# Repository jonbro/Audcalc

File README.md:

# AudCalc

AudCalc is a portable synthesizer and sequencer.

It has 8 voices which can switch between synthesis (using Mutable Instruments Braids cores) and sampling. The sequencer supports parameter locks, conditional triggers, and various time signatures and loop lengths. There are also two built in effects sends for building a full track. It's fun to jam with by itself, and can link into your larger portable music setup via midi or cv clock.

[Website](https://audcalc.jonathanbrodsky.com) | [Manual](https://audcalc.jonathanbrodsky.com/docs.html) | [Shop](https://thegoblingroup.com/products/audcalc) | [Contact](https://audcalc.jonathanbrodsky.com/contact.html)

## Specifications

### Synthesizer

- Many different oscillators from MI Braids
- 2 assignable AD envelopes
- Lowpass filter
- Volume, pan, legato, finetune
- 2 effects sends (delay & reverb)
- Assignable LFO
- Simple sampler (sampling via line in or onboard mic)
- 16 patches, 8 simultaneous monophonic voices

### Sequencer

- 16 patterns, with assignable lengths from 1-64 steps
- 4096 pattern lock locations for overriding synthesizer settings per step
- Each of the 16 patches can run at 2x-1/8 bpm rate, with some fun subdivisions
- Conditional triggers
- Pattern chaining
- Step ratcheting / retriggers

### Hardware

- RP2040 core
- 1000mAh rechargeable and replaceable battery, USB-C charging
- TRS midi in/out, audio in/out (3.5mm TRS), USB midi
- 100x65x25mm - approximately the size of a cassette tape box + knob height
- Body made with FDM black PLA, buttons with FDM translucent TPU
- FR4 (circuitboard) faceplate
- OLED display

## Building one

The BOM is contained within the Hardware KiCad project, ready for assembly via JLCPCB.
There are several additional items that must be sourced and assembled:

| part                         | count | mfg part number | link                                                  | notes                                                                                 |
|------------------------------|-------|-----------------|-------------------------------------------------------|---------------------------------------------------------------------------------------|
| oled screen (128x32)         | 1     | ssd1306         | https://www.aliexpress.com/item/4000842671330.html    | I'm using the white / solderable version.                                             |
| battery (50x34x5mm, ~1000mAh) | 1    | 503450          | search for "503450" with a JST-PH connector           | Widely available from many vendors. Confirm the correct polarity before using.        |
| m2 4mm f-f standoff          | 4     |                 | https://www.aliexpress.com/item/1005002145042844.html |                                                                                       |
| m2 6mm m-f standoff          | 4     |                 | https://www.aliexpress.com/item/1005002145042844.html |                                                                                       |
| m2 3mm hex head bolt (black) | 8     |                 | https://www.aliexpress.com/item/10000148429238.html   |                                                                                       |

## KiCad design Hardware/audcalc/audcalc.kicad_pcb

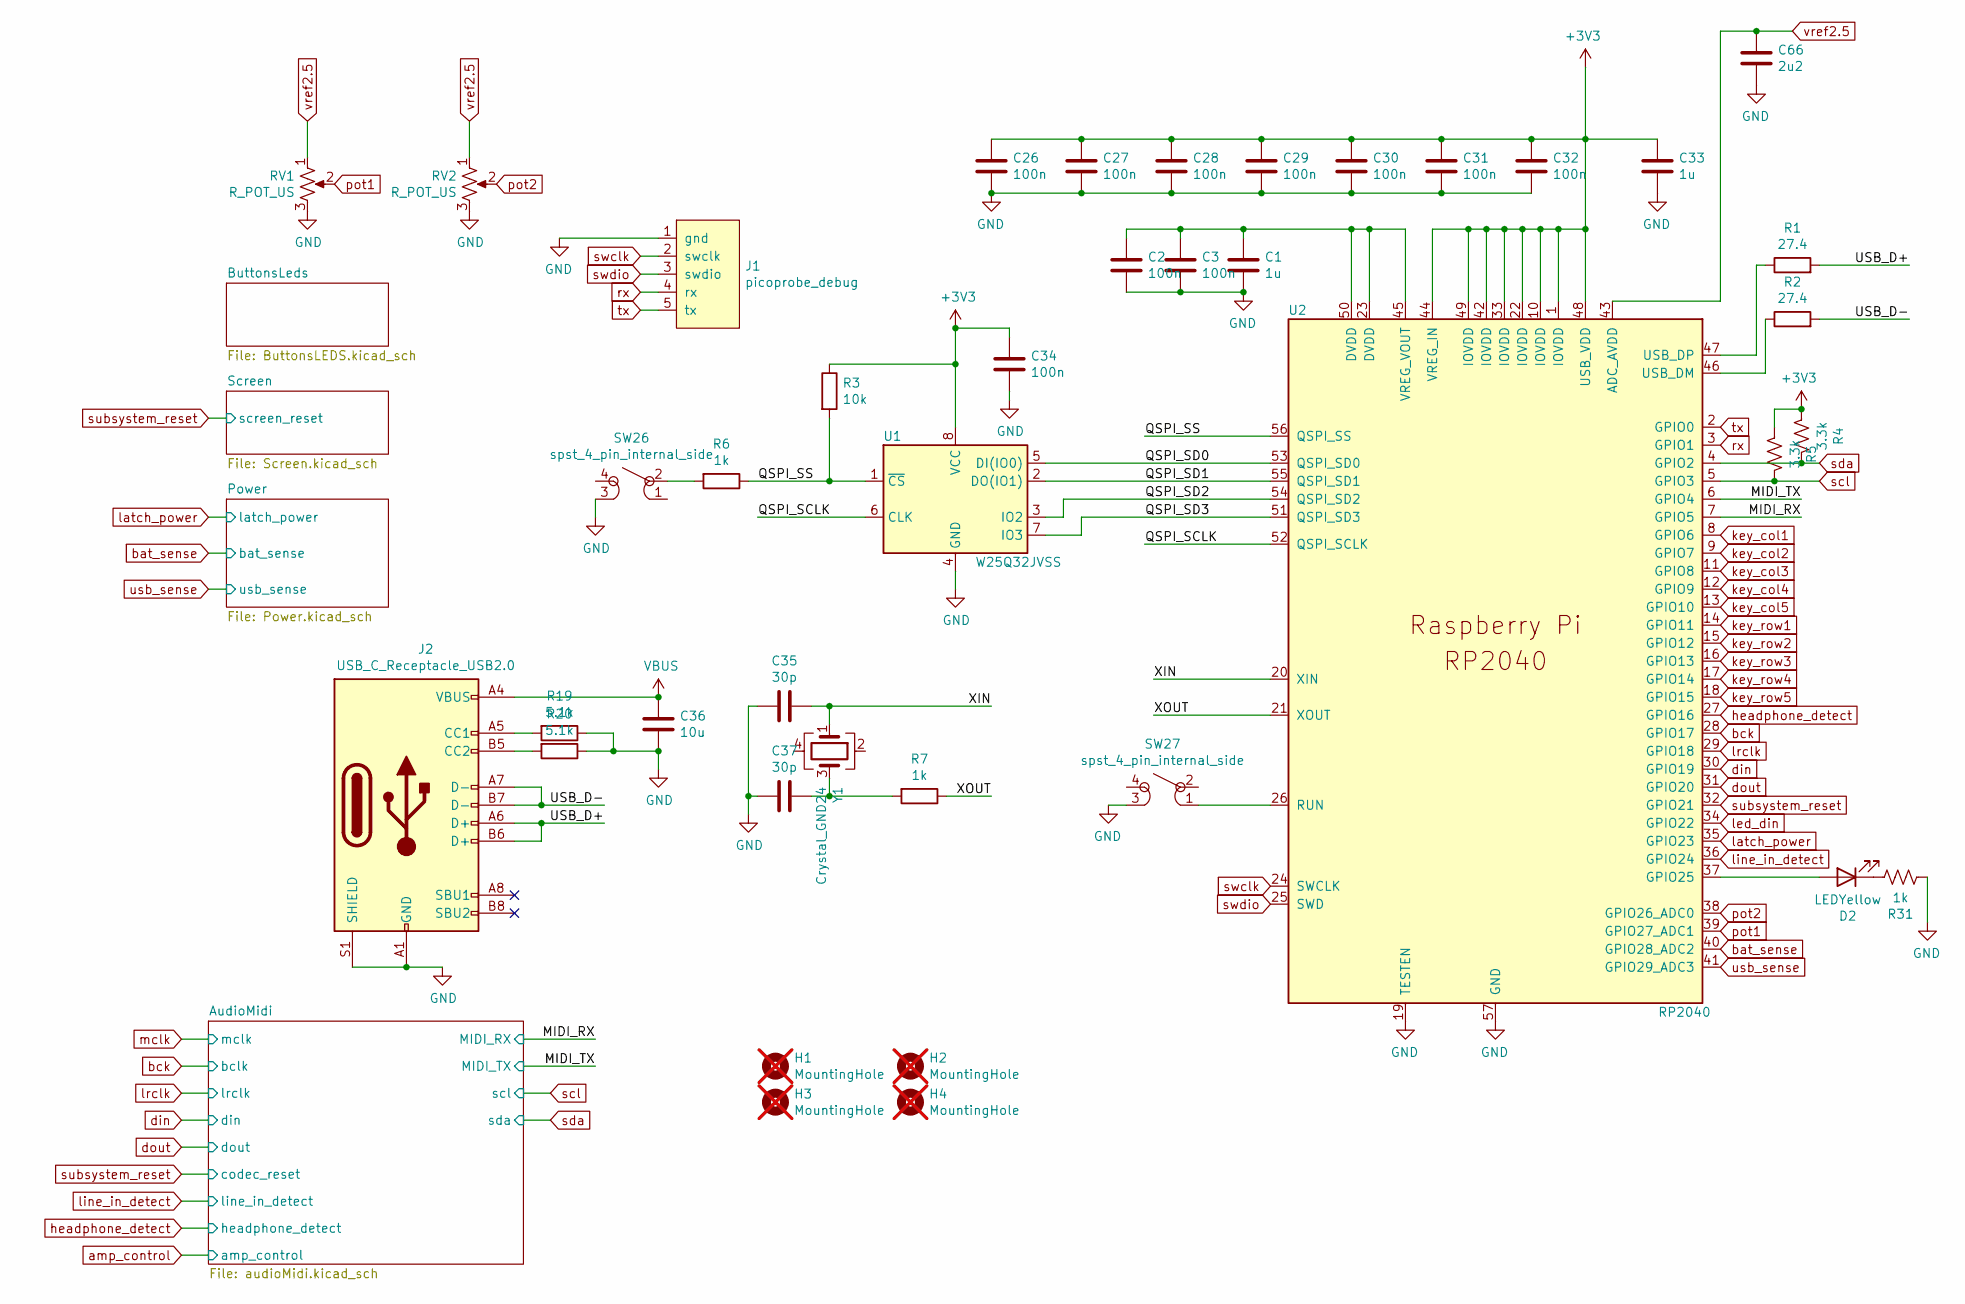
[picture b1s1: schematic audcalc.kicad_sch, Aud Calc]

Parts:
C1, C33: 1u; C_0402_1005Metric; LCSC C52923
C2, C3, C26, C27, C28, C29, C30, C31, C32, C34: 100n; C_0402_1005Metric; LCSC C307331
C35, C37: 30p; C_0402_1005Metric; LCSC C1570
C36: 10u; C_0402_1005Metric; LCSC C15525
C66: 2u2; C_0402_1005Metric; LCSC C12530
D2: LEDYellow; LED_0603; LCSC C89811
H1, H2, H3, H4: MountingHole; MountingHole_2.2mm_M2; not fitted
J1: picoprobe_debug; pico debug header
J2: USB_C_Receptacle_USB2.0; USB-C_SMD-TYPE-C-31-M-12; LCSC C165948
R1, R2: 27.4; R_0402_1005Metric_nosilk; LCSC C31439
R3: 10k; R_0402_1005Metric_nosilk; LCSC C25744
R4, R5: 3.3k; R_0402_1005Metric_nosilk; LCSC C25890
R6, R7, R31: 1k; R_0402_1005Metric_nosilk; LCSC C11702
R19, R20: 5.1k; R_0402_1005Metric_nosilk; LCSC C25905
RV1, RV2: R_POT_US; Potentiometer_Alps_RK09K_Horizontal; LCSC C209779
SW26, SW27: spst_4_pin_internal_side; SKSCLDE010; LCSC C115362
U1: W25Q32JVSS; SOIJ-8_5.3x5.3mm_Pitch1.27mm; LCSC C97521
U2: RP2040; RP2040-QFN-56; LCSC C2040
Y1: Crystal_GND24; Crystal_SMD_3225-4pin_3.2x2.5mm; LCSC C5332006

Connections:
+3V3: C26.1, C27.1, C28.1, C29.1, C30.1, C31.1, C32.1, C33.1, C34.1, R3.1, R4.1, R5.1, U1.8 (VCC), U2.1 (IOVDD), U2.10 (IOVDD), U2.22 (IOVDD), U2.33 (IOVDD), U2.42 (IOVDD), U2.44 (VREG_IN), U2.48 (USB_VDD), U2.49 (IOVDD); also elsewhere on the board
/MIDI_RX: U2.7 (GPIO5); also elsewhere on the board
/MIDI_TX: U2.6 (GPIO4); also elsewhere on the board
/QSPI_SCLK: U1.6 (CLK), U2.52 (QSPI_SCLK)
/QSPI_SD0: U1.5 (DI(IO0)), U2.53 (QSPI_SD0)
/QSPI_SD1: U1.2 (DO(IO1)), U2.55 (QSPI_SD1)
/QSPI_SD2: U1.3 (IO2), U2.54 (QSPI_SD2)
/QSPI_SD3: U1.7 (IO3), U2.51 (QSPI_SD3)
/QSPI_SS: R3.2, R6.1, U1.1 (~CS), U2.56 (QSPI_SS)
/USB_D+: J2.A6 (D+), J2.B6 (D+), R1.2
/USB_D-: J2.A7 (D-), J2.B7 (D-), R2.2
/XIN: C35.1, U2.20 (XIN), Y1.1
/XOUT: R7.1, U2.21 (XOUT)
GND: C1.2, C2.2, C3.2, C26.2, C27.2, C28.2, C29.2, C30.2, C31.2, C32.2, C33.2, C34.2, C35.2, C36.2, C37.2, C66.2, J1.1 (gnd), J2.A1 (GND), J2.A12 (GND), J2.B1 (GND), J2.B12 (GND), J2.S1 (SHIELD), R19.1, R20.1, R31.2, RV1.3, RV2.3, SW26.3, SW27.3, U1.4 (GND), U2.19 (TESTEN), U2.57 (GND); also elsewhere on the board
unnamed: C37.1, R7.2, Y1.3
unnamed: D2.2 (A), U2.37 (GPIO25)
unnamed: D2.1 (K), R31.1
unnamed: J2.A5 (CC1), R19.2
unnamed: J2.B5 (CC2), R20.2
unnamed: R6.2, SW26.2
unnamed: SW27.1, U2.26 (RUN)
unnamed: R2.1, U2.46 (USB_DM)
unnamed: R1.1, U2.47 (USB_DP)
unnamed: C1.1, C2.1, C3.1, U2.23 (DVDD), U2.45 (VREG_VOUT), U2.50 (DVDD)
VBUS: C36.1, J2.A4 (VBUS), J2.A9 (VBUS), J2.B4 (VBUS), J2.B9 (VBUS); also elsewhere on the board
bat_sense: U2.40 (GPIO28_ADC2); also elsewhere on the board
bck: U2.28 (GPIO17); also elsewhere on the board
din: U2.30 (GPIO19); also elsewhere on the board
dout: U2.31 (GPIO20); also elsewhere on the board
headphone_detect: U2.27 (GPIO16); also elsewhere on the board
key_col1: U2.8 (GPIO6); also elsewhere on the board
key_col2: U2.9 (GPIO7); also elsewhere on the board
key_col3: U2.11 (GPIO8); also elsewhere on the board
key_col4: U2.12 (GPIO9); also elsewhere on the board
key_col5: U2.13 (GPIO10); also elsewhere on the board
key_row1: U2.14 (GPIO11); also elsewhere on the board
key_row2: U2.15 (GPIO12); also elsewhere on the board
key_row3: U2.16 (GPIO13); also elsewhere on the board
key_row4: U2.17 (GPIO14); also elsewhere on the board
key_row5: U2.18 (GPIO15); also elsewhere on the board
latch_power: U2.35 (GPIO23); also elsewhere on the board
led_din: U2.34 (GPIO22); also elsewhere on the board
line_in_detect: U2.36 (GPIO24); also elsewhere on the board
lrclk: U2.29 (GPIO18); also elsewhere on the board
pot1: RV1.2, U2.39 (GPIO27_ADC1)
pot2: RV2.2, U2.38 (GPIO26_ADC0)
rx: J1.4 (rx), U2.3 (GPIO1)
scl: R5.2, U2.5 (GPIO3); also elsewhere on the board
sda: R4.2, U2.4 (GPIO2); also elsewhere on the board
subsystem_reset: U2.32 (GPIO21); also elsewhere on the board
swclk: J1.2 (swclk), U2.24 (SWCLK)
swdio: J1.3 (swdio), U2.25 (SWD)
tx: J1.5 (tx), U2.2 (GPIO0)
usb_sense: U2.41 (GPIO29_ADC3); also elsewhere on the board
vref2.5: C66.1, RV1.1, RV2.1, U2.43 (ADC_AVDD); also elsewhere on the board

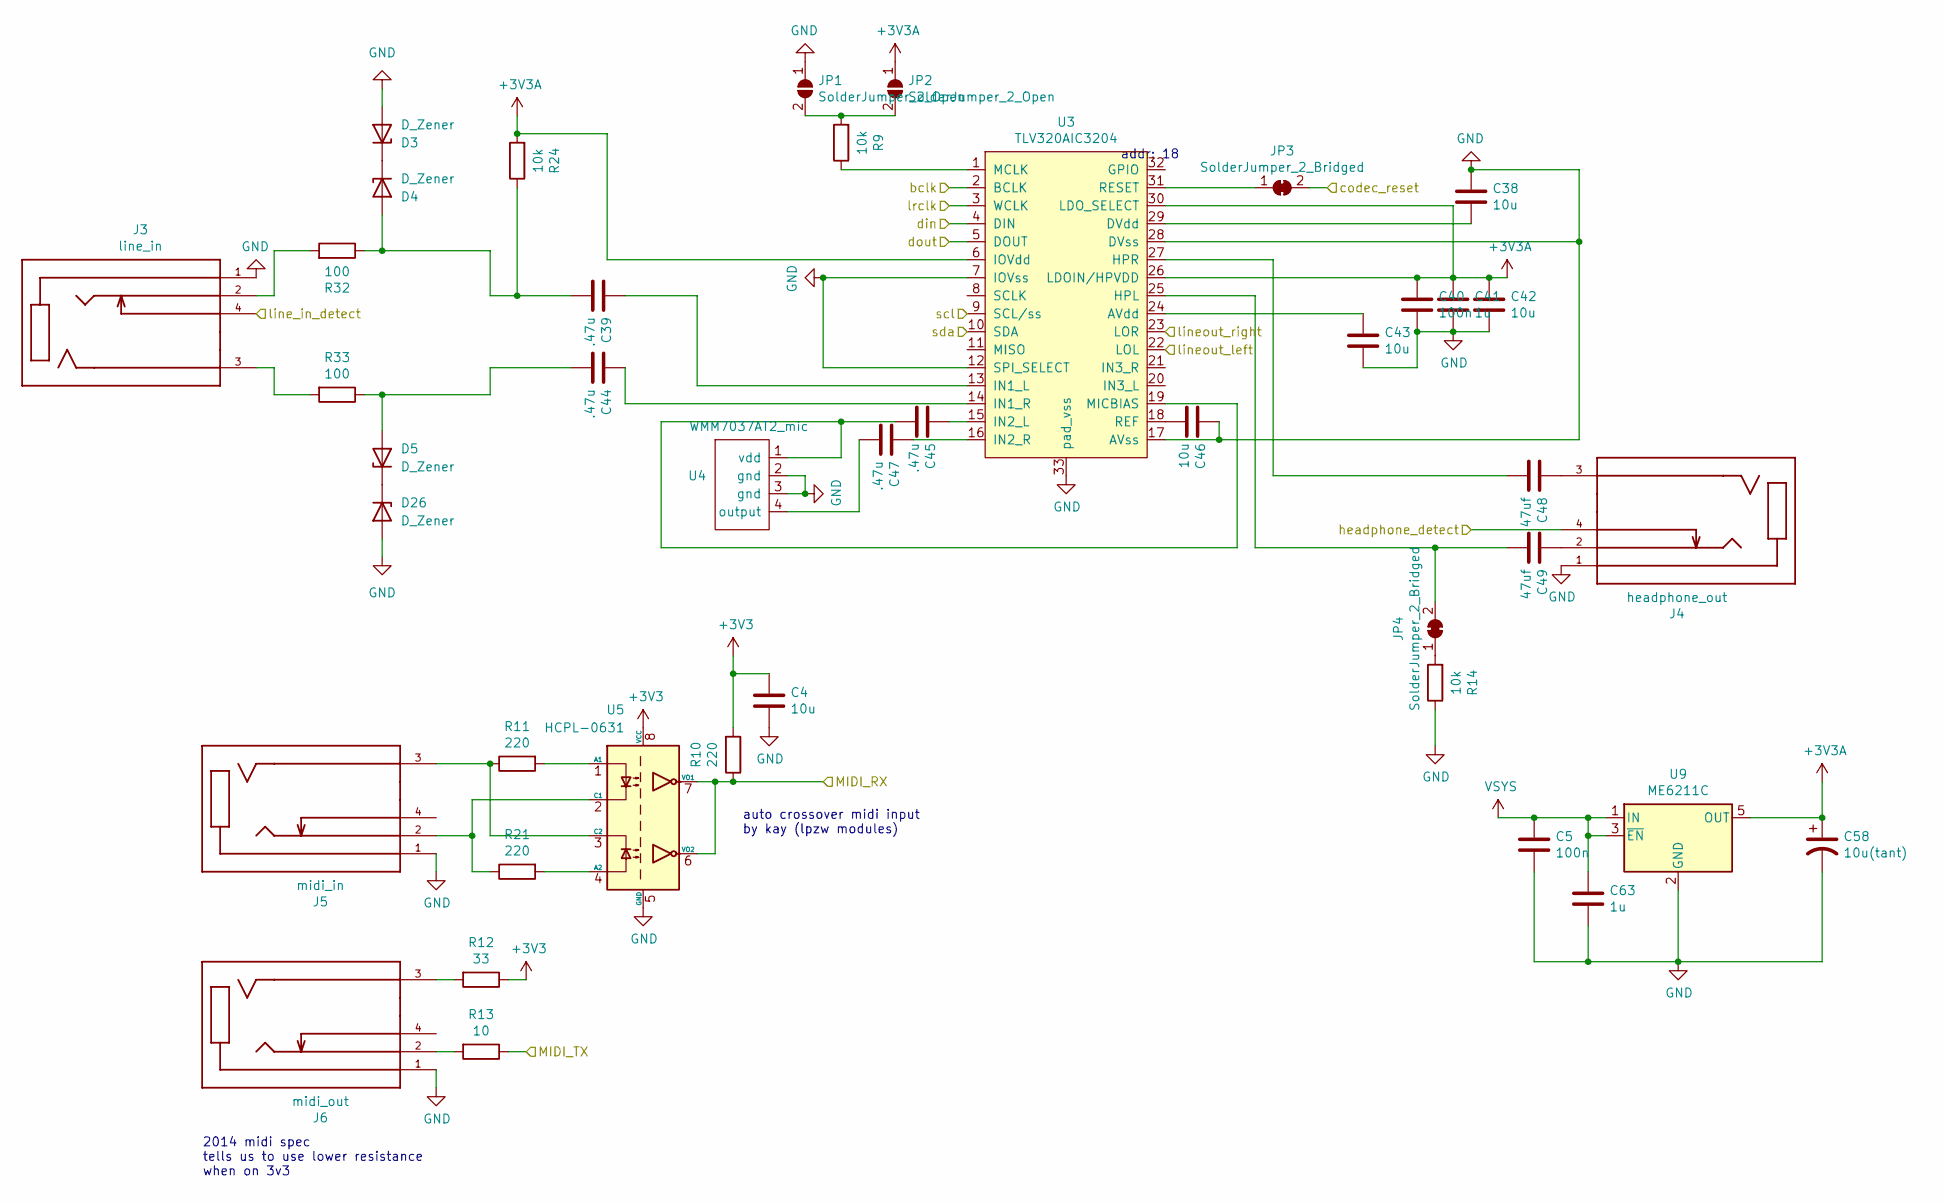
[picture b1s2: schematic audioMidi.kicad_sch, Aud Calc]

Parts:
C4, C38, C42, C43, C46: 10u; C_0402_1005Metric; LCSC C15525
C5, C40: 100n; C_0402_1005Metric; LCSC C307331
C39, C44, C45, C47: .47u; C_0603_nosilk; LCSC C1623
C41, C63: 1u; C_0402_1005Metric; LCSC C52923
C48, C49: 47uf; C_1206; LCSC C96123
C58: 10u(tant); CP_Tantalum_Case-A_EIA-3216-18_Reflow; LCSC C7171
D3, D4, D5, D26: D_Zener; D_SOD-323F; LCSC C52056
J3: line_in; HRO-PJ-327C-A; LCSC C145813
J4: headphone_out; HRO-PJ-327C-A; LCSC C145813
J5: midi_in; HRO-PJ-327C-A; LCSC C145813
J6: midi_out; HRO-PJ-327C-A; LCSC C145813
JP1, JP2: SolderJumper_2_Open; SolderJumper-2_P1.3mm_Open_RoundedPad1.0x1.5mm
JP3, JP4: SolderJumper_2_Bridged; SolderJumper-2_P1.3mm_Bridged_Pad1.0x1.5mm
R9, R14, R24: 10k; R_0402_1005Metric_nosilk; LCSC C25744
R10, R11, R21: 220; R_0402_1005Metric_nosilk; LCSC C25091
R12: 33; R_0402_1005Metric_nosilk; LCSC C25105
R13: 10; R_0402_1005Metric_nosilk; LCSC C25077
R32, R33: 100; R_0402_1005Metric; LCSC C25076
U3: TLV320AIC3204; QFN-32-1EP_5x5mm_Pitch0.5mm; LCSC C9925
U4: WMM7037AT2_mic; LGA-4 (3x3.8); LCSC C140705
U5: HCPL-0631; SOIC-8_3.9x4.9mm_P1.27mm; LCSC C43949
U9: ME6211C; SOT-23-5; LCSC C82942

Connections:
+3V3: C4.1, R10.2, R12.1, U5.8 (VCC); also elsewhere on the board
+3V3A: C40.1, C41.1, C42.1, C58.1, JP2.1 (A), R24.2, U3.6 (IOVdd), U3.26 (LDOIN/HPVDD), U3.30 (LDO_SELECT), U9.5 (OUT)
/AudioMidi/lineout_left: U3.22 (LOL)
/AudioMidi/lineout_right: U3.23 (LOR)
/MIDI_RX: R10.1, U5.6 (VO2), U5.7 (VO1); also elsewhere on the board
/MIDI_TX: R13.1; also elsewhere on the board
GND: C4.2, C5.2, C38.1, C40.2, C41.2, C42.2, C43.2, C46.1, C58.2, C63.2, D3.2 (A), D26.2 (A), J3.1 (SLEEVE), J4.1 (SLEEVE), J5.1 (SLEEVE), J6.1 (SLEEVE), JP1.1 (A), R14.1, U3.7 (IOVss), U3.12 (SPI_SELECT), U3.17 (AVss), U3.28 (DVss), U3.33 (pad_vss), U4.2 (gnd), U4.3 (gnd), U5.5 (GND), U9.2 (GND); also elsewhere on the board
unnamed: D3.1 (K), D4.1 (K)
unnamed: C39.2, D4.2 (A), R24.1, R32.1
unnamed: C44.2, D5.2 (A), R33.1
unnamed: D5.1 (K), D26.1 (K)
unnamed: J3.3 (RING), R33.2
unnamed: J3.2 (TIP_1), R32.2
unnamed: C48.1, J4.3 (RING)
unnamed: C49.1, J4.2 (TIP_1)
unnamed: J5.3 (RING), R11.1, U5.3 (C2)
unnamed: J5.2 (TIP_1), R21.1, U5.2 (C1)
unnamed: J6.3 (RING), R12.2
unnamed: J6.2 (TIP_1), R13.2
unnamed: JP1.2 (B), JP2.2 (B), R9.2
unnamed: JP3.1 (A), U3.31 (RESET)
unnamed: JP4.1 (A), R14.2
unnamed: C49.2, JP4.2 (B), U3.25 (HPL)
unnamed: C43.1, U3.24 (AVdd)
unnamed: C38.2, U3.29 (DVdd)
unnamed: C48.2, U3.27 (HPR)
unnamed: C39.1, U3.13 (IN1_L)
unnamed: C44.1, U3.14 (IN1_R)
unnamed: C45.1, U3.15 (IN2_L)
unnamed: C47.1, U3.16 (IN2_R)
unnamed: R9.1, U3.1 (MCLK)
unnamed: C45.2, U3.19 (MICBIAS), U4.1 (vdd)
unnamed: C46.2, U3.18 (REF)
unnamed: C47.2, U4.4 (output)
unnamed: R11.2, U5.1 (A1)
unnamed: R21.2, U5.4 (A2)
VSYS: C5.1, C63.1, U9.1 (IN), U9.3 (~EN); also elsewhere on the board
bck: U3.2 (BCLK); also elsewhere on the board
din: U3.4 (DIN); also elsewhere on the board
dout: U3.5 (DOUT); also elsewhere on the board
headphone_detect: J4.4 (TIP_SWITCH); also elsewhere on the board
line_in_detect: J3.4 (TIP_SWITCH); also elsewhere on the board
lrclk: U3.3 (WCLK); also elsewhere on the board
scl: U3.9 (SCL/ss); also elsewhere on the board
sda: U3.10 (SDA); also elsewhere on the board
subsystem_reset: JP3.2 (B); also elsewhere on the board

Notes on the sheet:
2014 midi spec tells us to use lower resistance when on 3v3
addr: 18
auto crossover midi input by kay (lpzw modules)

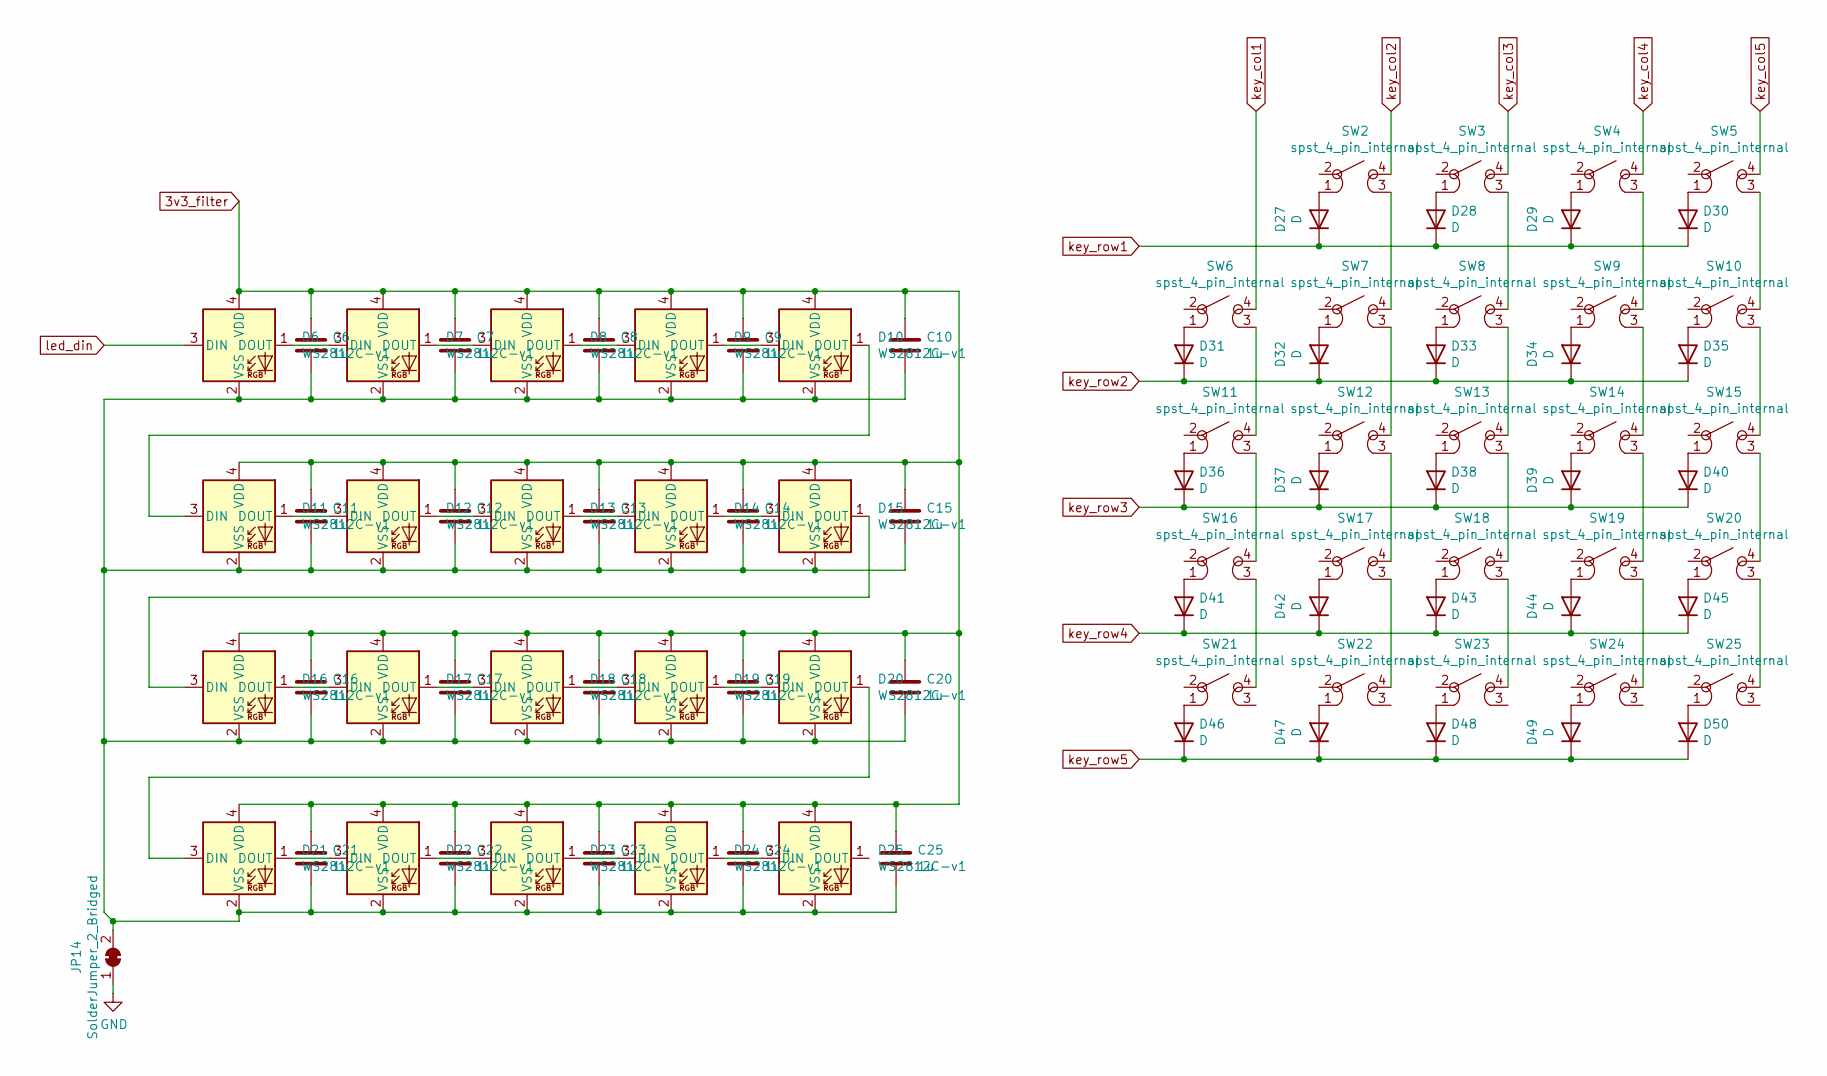
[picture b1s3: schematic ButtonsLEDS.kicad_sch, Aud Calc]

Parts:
C6, C7, C8, C9, C10, C11, C12, C13, C14, C15, C16, C17, C18, C19, C20, C21, C22, C23, C24, C25: 1u; C_0402_1005Metric; LCSC C52923
D6, D7, D8, D9, D10, D11, D12, D13, D14, D15, D16, D17, D18, D19, D20, D21, D22, D23, D24, D25: WS2812C-v1; ws2812b-2020-lightpipe; LCSC C2976072
D27, D28, D29, D30, D31, D32, D33, D34, D35, D36, D37, D38, D39, D40, D41, D42, D43, D44, D45, D46, D47, D48, D49, D50: D; D_SOD-323F_less_silk; LCSC C2128
JP14: SolderJumper_2_Bridged; SolderJumper-2_P1.3mm_Bridged_Pad1.0x1.5mm
SW2, SW3, SW4, SW5, SW6, SW7, SW8, SW9, SW10, SW11, SW12, SW13, SW14, SW15, SW16, SW17, SW18, SW19, SW20, SW21, SW22, SW23, SW24, SW25: spst_4_pin_internal; ts1187; LCSC C318884

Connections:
3v3_filter: C6.1, C7.1, C8.1, C9.1, C10.1, C11.1, C12.1, C13.1, C14.1, C15.1, C16.1, C17.1, C18.1, C19.1, C20.1, C21.1, C22.1, C23.1, C24.1, C25.1, D6.4 (VDD), D7.4 (VDD), D8.4 (VDD), D9.4 (VDD), D10.4 (VDD), D11.4 (VDD), D12.4 (VDD), D13.4 (VDD), D14.4 (VDD), D15.4 (VDD), D16.4 (VDD), D17.4 (VDD), D18.4 (VDD), D19.4 (VDD), D20.4 (VDD), D21.4 (VDD), D22.4 (VDD), D23.4 (VDD), D24.4 (VDD), D25.4 (VDD); also elsewhere on the board
GND: JP14.1 (A); also elsewhere on the board
unnamed: D6.1 (DOUT), D7.3 (DIN)
unnamed: D7.1 (DOUT), D8.3 (DIN)
unnamed: D8.1 (DOUT), D9.3 (DIN)
unnamed: D9.1 (DOUT), D10.3 (DIN)
unnamed: D10.1 (DOUT), D11.3 (DIN)
unnamed: C6.2, C7.2, C8.2, C9.2, C10.2, C11.2, C12.2, C13.2, C14.2, C15.2, C16.2, C17.2, C18.2, C19.2, C20.2, C21.2, C22.2, C23.2, C24.2, C25.2, D6.2 (VSS), D7.2 (VSS), D8.2 (VSS), D9.2 (VSS), D10.2 (VSS), D11.2 (VSS), D12.2 (VSS), D13.2 (VSS), D14.2 (VSS), D15.2 (VSS), D16.2 (VSS), D17.2 (VSS), D18.2 (VSS), D19.2 (VSS), D20.2 (VSS), D21.2 (VSS), D22.2 (VSS), D23.2 (VSS), D24.2 (VSS), D25.2 (VSS), JP14.2 (B)
unnamed: D11.1 (DOUT), D12.3 (DIN)
unnamed: D12.1 (DOUT), D13.3 (DIN)
unnamed: D13.1 (DOUT), D14.3 (DIN)
unnamed: D14.1 (DOUT), D15.3 (DIN)
unnamed: D15.1 (DOUT), D16.3 (DIN)
unnamed: D16.1 (DOUT), D17.3 (DIN)
unnamed: D17.1 (DOUT), D18.3 (DIN)
unnamed: D18.1 (DOUT), D19.3 (DIN)
unnamed: D19.1 (DOUT), D20.3 (DIN)
unnamed: D20.1 (DOUT), D21.3 (DIN)
unnamed: D21.1 (DOUT), D22.3 (DIN)
unnamed: D22.1 (DOUT), D23.3 (DIN)
unnamed: D23.1 (DOUT), D24.3 (DIN)
unnamed: D24.1 (DOUT), D25.3 (DIN)
unnamed: D27.2 (A), SW2.1
unnamed: D28.2 (A), SW3.1
unnamed: D29.2 (A), SW4.1
unnamed: D30.2 (A), SW5.1
unnamed: D31.2 (A), SW6.1
unnamed: D32.2 (A), SW7.1
unnamed: D33.2 (A), SW8.1
unnamed: D34.2 (A), SW9.1
unnamed: D35.2 (A), SW10.1
unnamed: D36.2 (A), SW11.1
unnamed: D37.2 (A), SW12.1
unnamed: D38.2 (A), SW13.1
unnamed: D39.2 (A), SW14.1
unnamed: D40.2 (A), SW15.1
unnamed: D41.2 (A), SW16.1
unnamed: D42.2 (A), SW17.1
unnamed: D43.2 (A), SW18.1
unnamed: D44.2 (A), SW19.1
unnamed: D45.2 (A), SW20.1
unnamed: D46.2 (A), SW21.1
unnamed: D47.2 (A), SW22.1
unnamed: D48.2 (A), SW23.1
unnamed: D49.2 (A), SW24.1
unnamed: D50.2 (A), SW25.1
unnamed: SW2.3, SW7.4
unnamed: SW3.3, SW8.4
unnamed: SW4.3, SW9.4
unnamed: SW10.3, SW15.4
unnamed: SW5.3, SW10.4
unnamed: SW11.3, SW16.4
unnamed: SW6.3, SW11.4
unnamed: SW12.3, SW17.4
unnamed: SW7.3, SW12.4
unnamed: SW13.3, SW18.4
unnamed: SW8.3, SW13.4
unnamed: SW14.3, SW19.4
unnamed: SW9.3, SW14.4
unnamed: SW15.3, SW20.4
unnamed: SW16.3, SW21.4
unnamed: SW17.3, SW22.4
unnamed: SW18.3, SW23.4
unnamed: SW19.3, SW24.4
unnamed: SW20.3, SW25.4
key_col1: SW6.4; also elsewhere on the board
key_col2: SW2.4; also elsewhere on the board
key_col3: SW3.4; also elsewhere on the board
key_col4: SW4.4; also elsewhere on the board
key_col5: SW5.4; also elsewhere on the board
key_row1: D27.1 (K), D28.1 (K), D29.1 (K), D30.1 (K); also elsewhere on the board
key_row2: D31.1 (K), D32.1 (K), D33.1 (K), D34.1 (K), D35.1 (K); also elsewhere on the board
key_row3: D36.1 (K), D37.1 (K), D38.1 (K), D39.1 (K), D40.1 (K); also elsewhere on the board
key_row4: D41.1 (K), D42.1 (K), D43.1 (K), D44.1 (K), D45.1 (K); also elsewhere on the board
key_row5: D46.1 (K), D47.1 (K), D48.1 (K), D49.1 (K), D50.1 (K); also elsewhere on the board
led_din: D6.3 (DIN); also elsewhere on the board

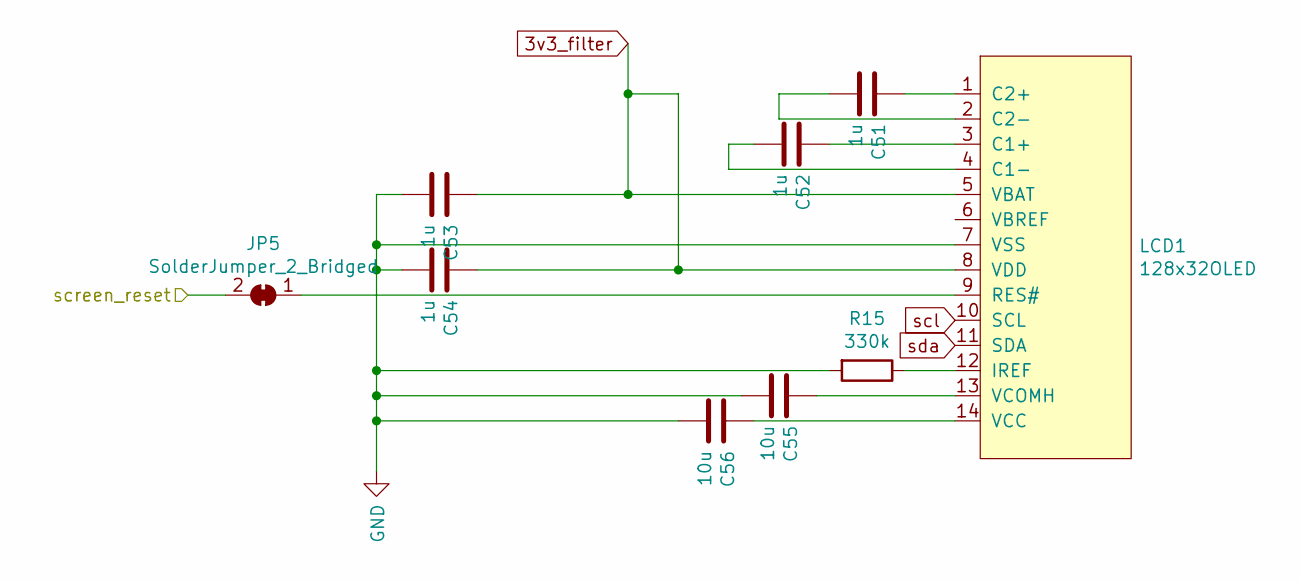
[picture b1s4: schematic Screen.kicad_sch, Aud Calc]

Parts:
C51, C52, C53, C54: 1u; C_0402_1005Metric; LCSC C52923
C55, C56: 10u; C_0402_1005Metric; LCSC C15525
JP5: SolderJumper_2_Bridged; SolderJumper-2_P1.3mm_Bridged_Pad1.0x1.5mm
LCD1: 128x32OLED; oled_ssd1306_14pin_91
R15: 330k; R_0402_1005Metric; LCSC C25778

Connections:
3v3_filter: C53.1, C54.1, LCD1.5 (VBAT), LCD1.8 (VDD); also elsewhere on the board
GND: C53.2, C54.2, C55.2, C56.2, LCD1.7 (VSS), R15.2; also elsewhere on the board
unnamed: JP5.1 (A), LCD1.9 (RES#)
unnamed: C52.1, LCD1.3 (C1+)
unnamed: C52.2, LCD1.4 (C1-)
unnamed: C51.1, LCD1.1 (C2+)
unnamed: C51.2, LCD1.2 (C2-)
unnamed: LCD1.12 (IREF), R15.1
unnamed: C56.1, LCD1.14 (VCC)
unnamed: C55.1, LCD1.13 (VCOMH)
scl: LCD1.10 (SCL); also elsewhere on the board
sda: LCD1.11 (SDA); also elsewhere on the board
subsystem_reset: JP5.2 (B); also elsewhere on the board

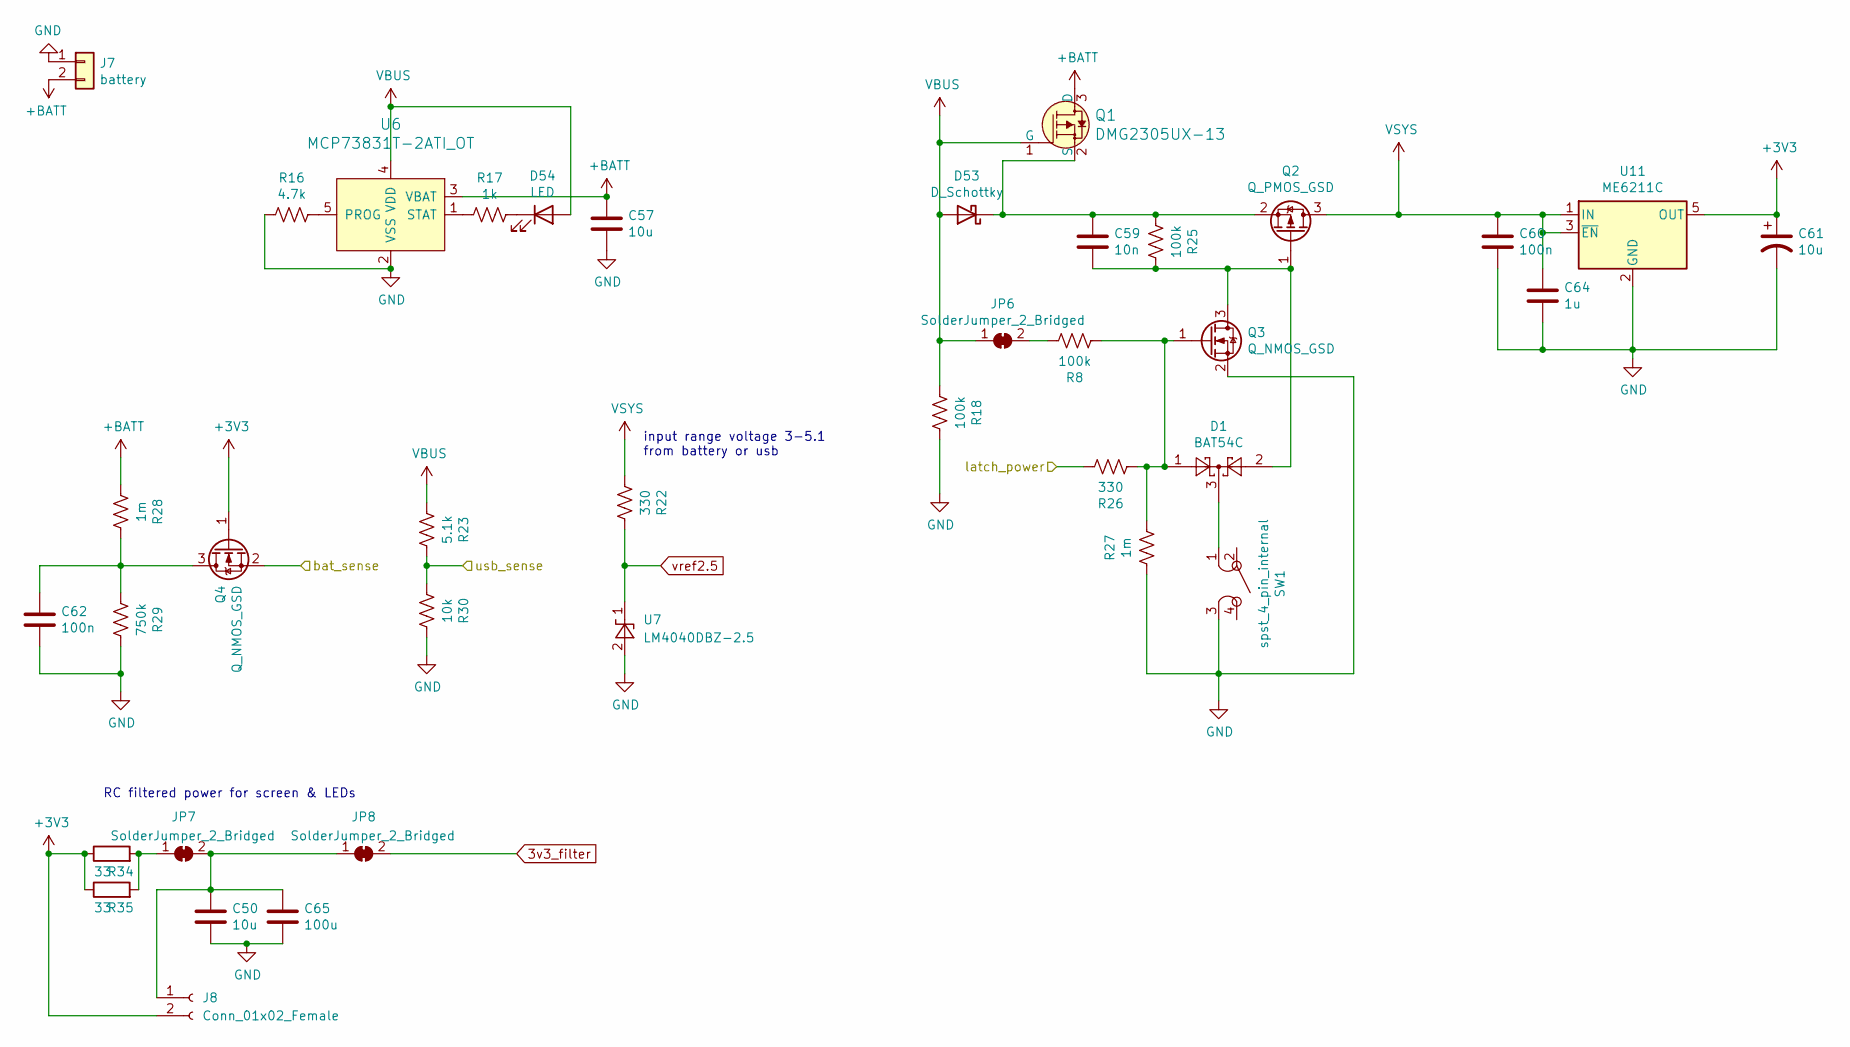
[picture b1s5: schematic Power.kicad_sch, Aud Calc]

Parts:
C50, C57, C61: 10u; C_0402_1005Metric; LCSC C15525
C59: 10n; C_0402_1005Metric; LCSC C15195
C60, C62: 100n; C_0402_1005Metric; LCSC C307331
C64: 1u; C_0402_1005Metric; LCSC C52923
C65: 100u; CP_EIA-3528-21_Kemet-B; LCSC C16133
D1: BAT54C; SOT-23; LCSC C37704
D53: D_Schottky; D_SMA; LCSC C14996
D54: LED; LED_0603; LCSC C2286
J7: battery; JST_PH_S2B-PH-SM4-TB_02x2.00mm_Angled; LCSC C3029440
J8: Conn_01x02_Female; PinHeader_1x02_P2.54mm_Vertical
JP6, JP7, JP8: SolderJumper_2_Bridged; SolderJumper-2_P1.3mm_Bridged_Pad1.0x1.5mm
Q1: DMG2305UX-13; SOT-23-3; LCSC C144153
Q2: Q_PMOS_GSD; SOT-23; LCSC C15127
Q3, Q4: Q_NMOS_GSD; SOT-23; LCSC C79015
R8, R18, R25: 100k; R_0402_1005Metric_nosilk; LCSC C25741
R16: 4.7k; R_0402_1005Metric_nosilk; LCSC C25900
R17: 1k; R_0402_1005Metric_nosilk; LCSC C11702
R22, R26: 330; R_0402_1005Metric_nosilk; LCSC C25104
R23: 5.1k; R_0402_1005Metric_nosilk; LCSC C25905
R27, R28: 1m; R_0402_1005Metric_nosilk; LCSC C26083
R29: 750k; C_0603_nosilk; LCSC C23240
R30: 10k; R_0402_1005Metric_nosilk; LCSC C25744
R34, R35: 33; R_0402_1005Metric_nosilk; LCSC C25105
SW1: spst_4_pin_internal; ts1187; LCSC C318884
U6: MCP73831T-2ATI_OT; SOT-23-5; LCSC C14879
U7: LM4040DBZ-2.5; SOT-23; LCSC C460607
U11: ME6211C; SOT-23-5; LCSC C82942

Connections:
3v3_filter: JP8.2 (B); also elsewhere on the board
+3V3: C61.1, J8.2, Q4.1 (G), R34.1, R35.1, U11.5 (OUT); also elsewhere on the board
+BATT: C57.1, J7.2, Q1.3 (D), R28.2, U6.3 (VBAT)
GND: C50.2, C57.2, C60.2, C61.2, C62.2, C64.2, C65.2, J7.1, Q3.2 (S), R16.2, R18.1, R27.2, R29.1, R30.1, SW1.3, U6.2 (VSS), U7.2 (A), U11.2 (GND); also elsewhere on the board
unnamed: D1.3, SW1.1
unnamed: C59.1, D53.1 (K), Q1.2 (S), Q2.2 (S), R25.2
unnamed: D54.1 (K), R17.1
unnamed: C50.1, C65.1, J8.1, JP7.2 (B), JP8.1 (A)
unnamed: JP6.2 (B), R8.1
unnamed: JP7.1 (A), R34.2, R35.2
unnamed: C59.2, D1.2, Q2.1 (G), Q3.3 (D), R25.1
unnamed: D1.1, Q3.1 (G), R8.2, R26.2, R27.1
unnamed: C62.1, Q4.3 (D), R28.1, R29.2
unnamed: R16.1, U6.5 (PROG)
unnamed: R17.2, U6.1 (STAT)
VBUS: D53.2 (A), D54.2 (A), JP6.1 (A), Q1.1 (G), R18.2, R23.2, U6.4 (VDD); also elsewhere on the board
VSYS: C60.1, C64.1, Q2.3 (D), R22.2, U11.1 (IN), U11.3 (~EN); also elsewhere on the board
bat_sense: Q4.2 (S); also elsewhere on the board
latch_power: R26.1; also elsewhere on the board
usb_sense: R23.1, R30.2; also elsewhere on the board
vref2.5: R22.1, U7.1 (K); also elsewhere on the board

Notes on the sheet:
RC filtered power for screen & LEDs
input range voltage 3-5.1 from battery or usb

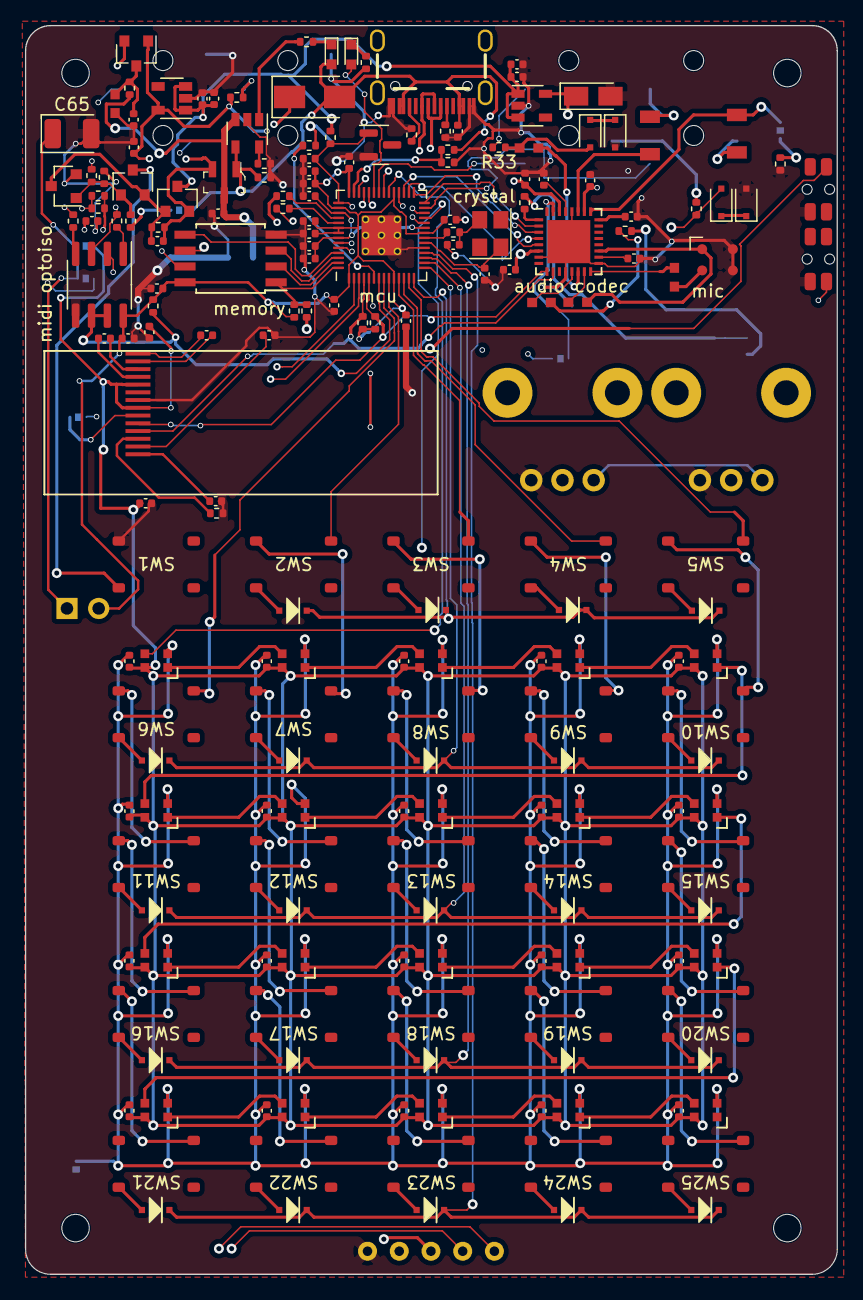
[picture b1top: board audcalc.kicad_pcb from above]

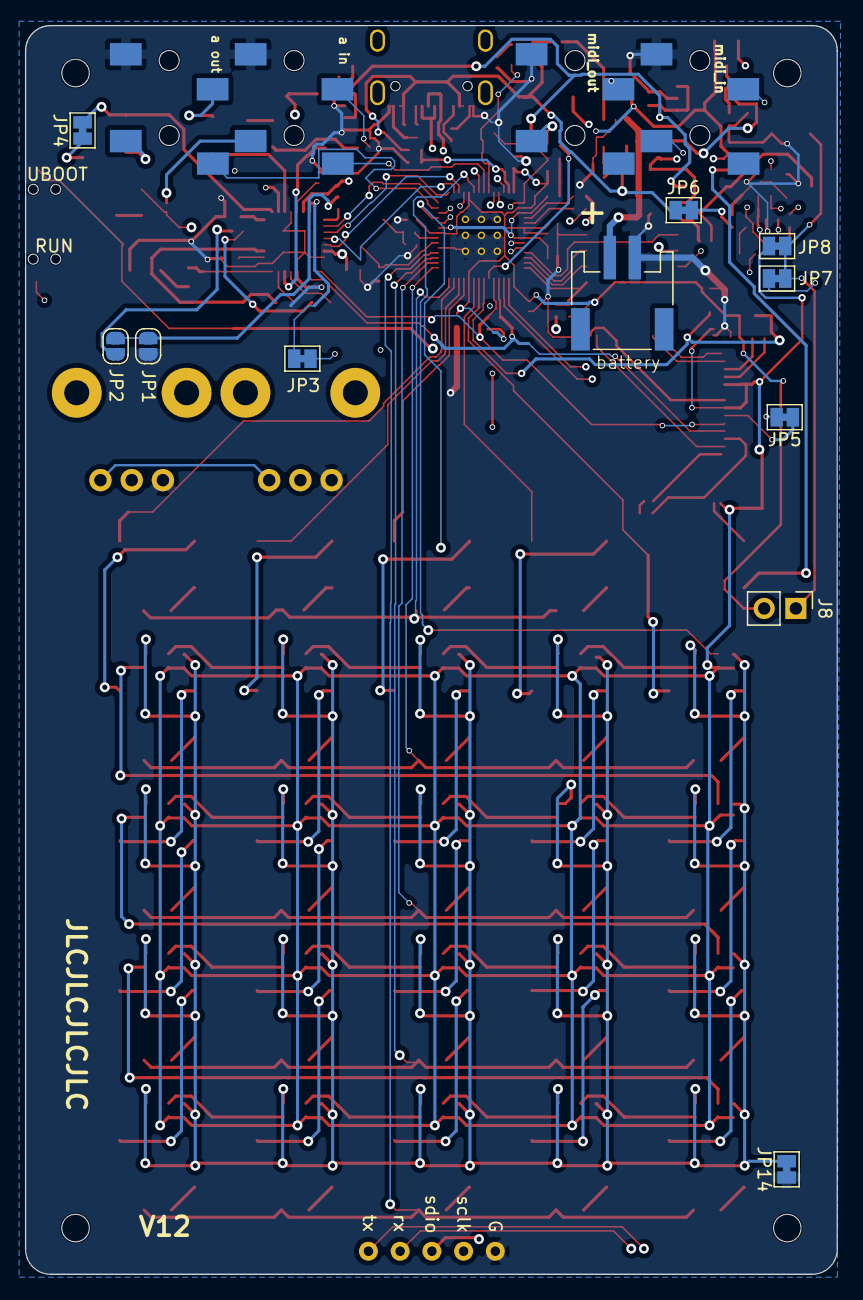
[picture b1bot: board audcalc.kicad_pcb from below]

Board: 4 copper layers, 65.0 x 100.0 mm, 218 parts (16 on the bottom side), 170 nets.

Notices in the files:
parts and their libraries:
Copyright 2016 Accelerated Designs. All rights reserved.
